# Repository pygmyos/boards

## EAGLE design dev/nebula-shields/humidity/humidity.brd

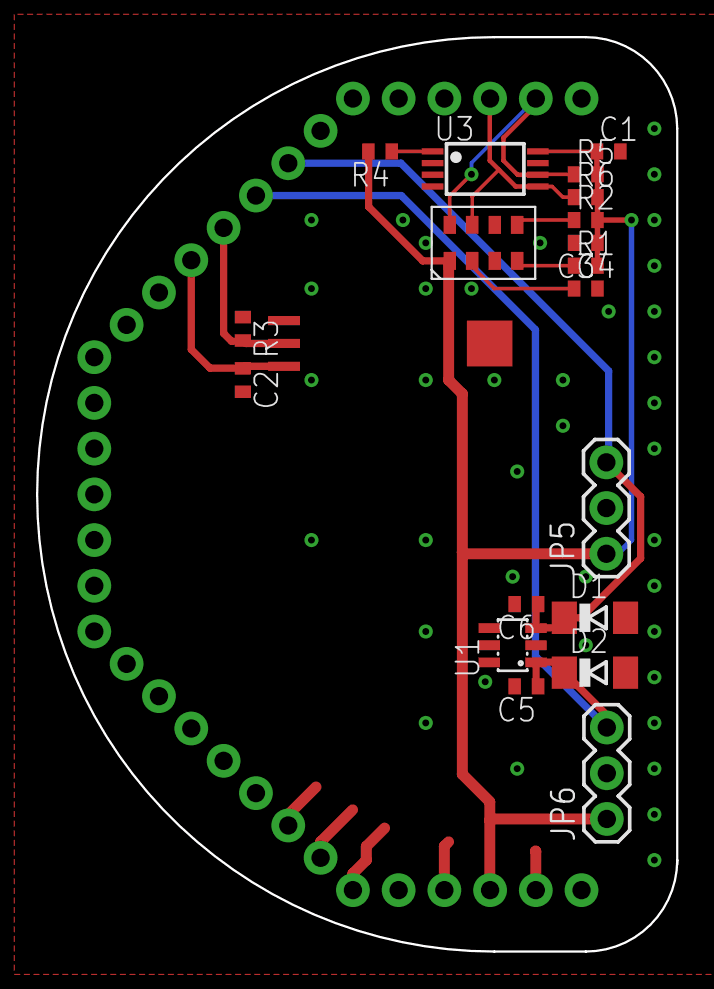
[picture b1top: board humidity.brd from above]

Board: 2 copper layers, 35.6 x 50.8 mm, 24 parts (0 on the bottom side), 12 nets.

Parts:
C1, C2: 0.1uF; C0402
C3, C4: 1uF; C0402
C5, C6: 33pF; C0402
D1, D2: 3.3V; SOD80C
INFO2: Warren D Greenway and Evan Teitelman; %CC-NC-SA
JP5, JP6: JUMPER-3PTH; 1X03
LOGO1: #LOGOA-THICK
NEBULA1: #NEBULAPTH; #NEBULA-PTH@1
NEBULAPART1: #NEBULA-PARTLABELS-BOTTOM; #NEBULA-LABELS-BOTT
R1, R2, R4: 47K; R0402
R3: 15K; R0402
R5, R6: 10K; R0402
U1: ESDAXXSC6; SOT23-6L
U2: HIH-5030
U3: EEPROM-ATMEL-AT24HC02B; TSSOP8
U4: PRESSURE-FREESCALE-MPL115A1; LGA8

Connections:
3.3V: C1.1, C3.1, JP5.1, JP6.1, NEBULA1.3.3V, R1.2, R2.2, R4.2, R5.2, R6.2, U3.8, U4.P1
GND: C1.2, C2.2, C3.2, C4.2, C5.2, C6.2, D1.A, D2.A, JP5.2, JP6.2, NEBULA1.GND1, NEBULA1.GND2, NEBULA1.GND3, NEBULA1.GND4, NEBULA1.GND5, R3.1, U1.2, U1.5, U2.P$2, U3.2, U3.3, U3.4, U3.7, U4.P3
unnamed: R4.1, U3.1
unnamed: C4.1, U4.P2
PWR: C2.1, NEBULA1.A3, U2.P$4
RST: R2.1, U4.P5
SCL: NEBULA1.COM1_TX, R5.1, U3.6, U4.P8
SDA: NEBULA1.COM1_RX, R6.1, U3.5, U4.P7
SENSOR: NEBULA1.A2, R3.2, U2.P$3
SHDN: R1.1, U4.P4
VOLT1: C6.1, D1.C, JP5.3, NEBULA1.A0, U1.3
VOLT2: C5.1, D2.C, JP6.3, NEBULA1.A1, U1.1

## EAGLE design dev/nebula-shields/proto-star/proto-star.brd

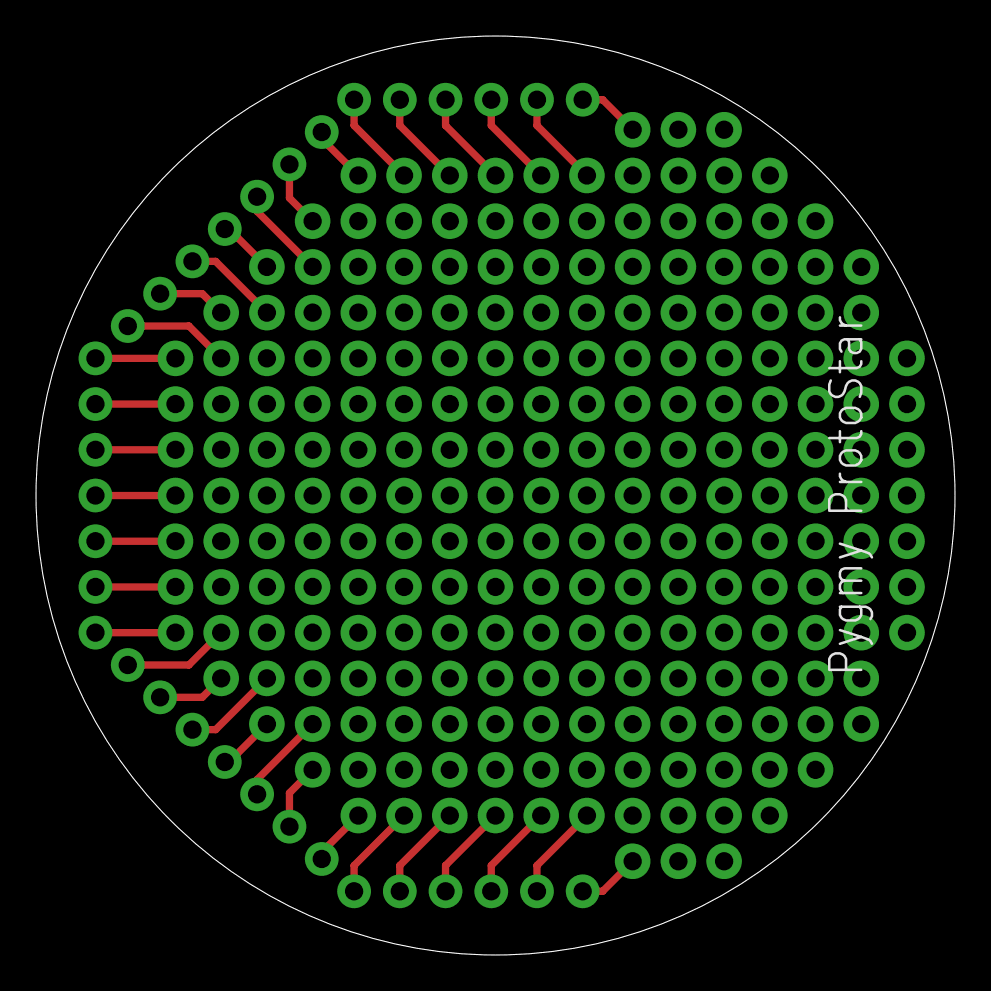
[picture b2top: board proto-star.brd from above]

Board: 2 copper layers, 51.1 x 51.1 mm, 35 parts (0 on the bottom side), 33 nets.

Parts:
FP1: #NEBULAPTH; #NEBULA-PTH
INFO2: Evan Teitelman and Warren D Greenway; %CC-NC-SA
TP1, TP2, TP3, TP4, TP5, TP6, TP7, TP8, TP9, TP10, TP11, TP12, TP13, TP14, TP15, TP16, TP17, TP35, TP36, TP37, TP38, TP39, TP40, TP41, TP42, TP43, TP44, TP45, TP46, TP47, TP48, TP49, TP50: NEBULA-TP

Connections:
unnamed: FP1.MCO, TP1.P$1
unnamed: FP1.COM1_TX, TP2.P$1
unnamed: FP1.COM1_RX, TP3.P$1
unnamed: FP1.T0, TP4.P$1
unnamed: FP1.T1, TP5.P$1
unnamed: FP1.T2, TP6.P$1
unnamed: FP1.T3, TP7.P$1
unnamed: FP1.A0, TP8.P$1
unnamed: FP1.A1, TP9.P$1
unnamed: FP1.A2, TP10.P$1
unnamed: FP1.A3, TP11.P$1
unnamed: FP1.D3, TP12.P$1
unnamed: FP1.D2, TP13.P$1
unnamed: FP1.D1, TP14.P$1
unnamed: FP1.D0, TP15.P$1
unnamed: FP1.A4, TP16.P$1
unnamed: FP1.A5, TP17.P$1
unnamed: FP1.COM2_TX, TP35.P$1
unnamed: FP1.COM2_RX, TP36.P$1
unnamed: FP1.DAC1, TP37.P$1
unnamed: FP1.DAC2, TP38.P$1
unnamed: FP1.TA0, TP39.P$1
unnamed: FP1.TA1, TP40.P$1
unnamed: FP1.A6, TP41.P$1
unnamed: FP1.A7, TP42.P$1
unnamed: FP1.GND5, TP43.P$1
unnamed: FP1.GND4, TP44.P$1
unnamed: FP1.GND3, TP45.P$1
unnamed: FP1.5V, TP46.P$1
unnamed: FP1.GND2, TP47.P$1
unnamed: FP1.3.3V, TP48.P$1
unnamed: FP1.GND1, TP49.P$1
unnamed: FP1.BAT, TP50.P$1

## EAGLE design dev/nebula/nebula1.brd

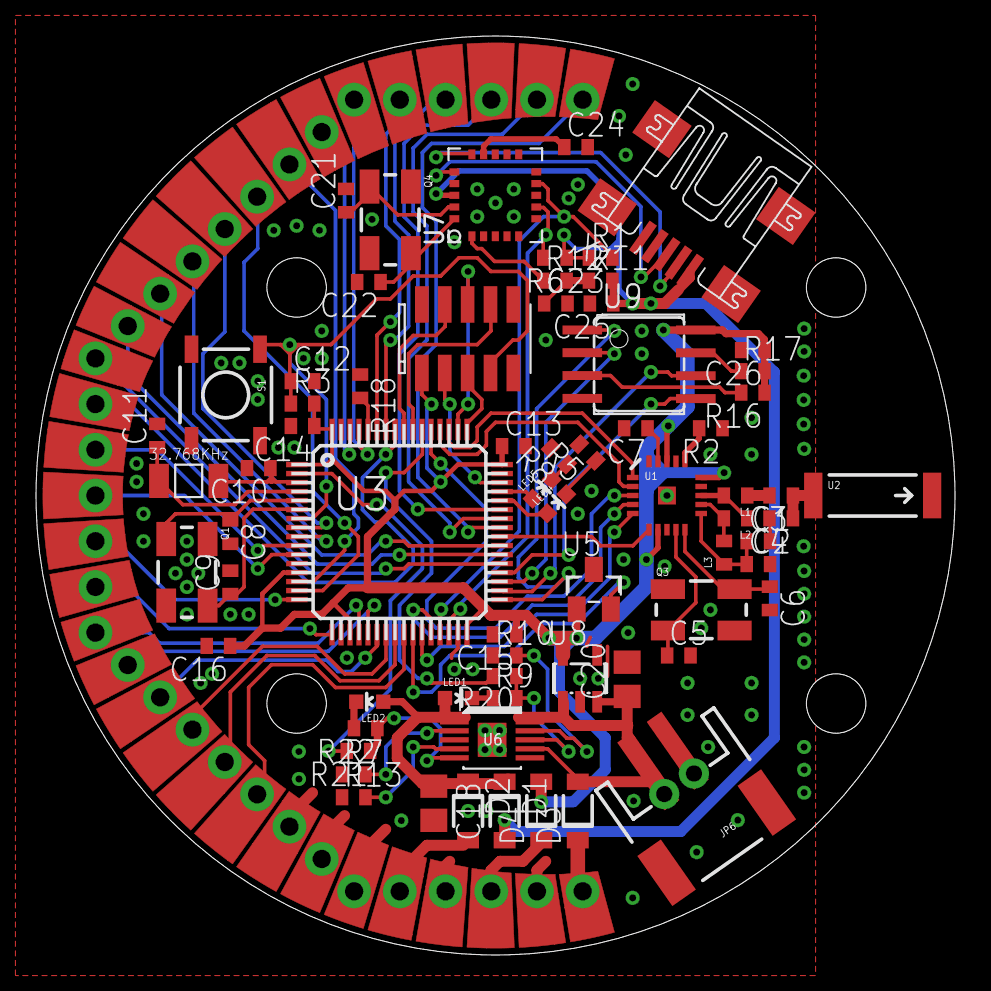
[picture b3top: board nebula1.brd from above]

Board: 2 copper layers, 51.1 x 51.1 mm, 80 parts (1 on the bottom side), 88 nets.

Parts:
C1: 1.5pF; C0402
C2: 1.0pF; C0402
C3: 0.0022uF; C0402
C4: 4.7pF; C0402
C5, C6, C8, C9, C21, C22: 18pF; C0402
C7: 0.033uF; C0402
C10, C11: 9pF; C0402
C12: 220pF; C0402
C13, C14, C15, C16, C23, C25, C26: 0.1uF; C0402
C18, C20: 10uF; C0805
C24: 0.47uF; C0402
D1, D2, D3, D4: SMF5.0AT1; SOD123FL
INFO3: Warren D Greenway and Evan Teitelman; %CC-NC-SA
JP6: JST-2-SMD
L1: 3.9nH; C0402
L2: 8.2nH; C0402
L3: 2.7nH; C0402
LED1: ORANGE; LED-0603
LED2: YELLOW; LED-0603
LED4: BLUE; LED-0603
LED5: GREEN; LED-0603
LOGO1: #LOGOA-THICK
NEBULA1: #NEBULAPTH; #NEBULA-PTH@1
NEBULAPART1: #NEBULA-PARTCOPPER; #NEBULA-COPPER
NEBULAPART2: #NEBULA-PARTRESTRICT; #NEBULA-RESTRICT
NEBULAPART3: #NEBULA-PARTSTOP; #NEBULA-STOP
NEBULAPART4: #NEBULA-PARTLABELS-BOTTOM; #NEBULA-LABELS-BOTT
Q1, Q4: 12MHz; CRYSTAL-SMD-5X3
Q2: CM415
Q3: 16MHz; CRYSTAL-SMD-5X3
R1, R6, R17, R18: 47K; R0402
R2: 22K; R0402
R3, R16: 100K; R0402
R5, R8, R9, R12, R22: 470; R0402
R7, R13: 1K; R0402
R10, R11, R20, R21: 10K; R0402
S1: TACTILE_SWITCH_SMD
U1: NRF24L01SMD; QFN20
U2: ANTENNA2SMD5; ANTENNA-CHIP5
U3: STM32F100R4T6B; S-PQFP64-G64
U4: STM32-JTAG-10P
U5: MICROCHIP-TEMP-TC1047; SOT23
U6: BQ24090; R-PDSO-G10
U7: MICROCHIP-USB-MCP2200; QFN-20-5X5
U8: NCP500; SOT23-5L
U9: SST25VF080B; SOIC8@1
U$1, U$2, U$3, U$4: STAND-OFF
X1: MINI-USB-UX60A-MB-5ST; UX60A-MB-5ST

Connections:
3.3V: C13.1, C14.1, C15.1, C16.1, C26.1, D4.A, R3.2, R16.1, R17.2, U1.7, U1.15, U1.18, U3.1, U3.13, U3.19, U3.32, U3.48, U3.64, U4.1, U5.1, U8.5, U9.8
5V: C18.1, D1.C, D2.C, LED1.A, LED2.A, U6.P$1
A0: NEBULA1.A0, U3.14
A1: NEBULA1.A1, U3.15
A2: NEBULA1.A2, U3.8
A3: NEBULA1.A3, U3.9
A4: NEBULA1.A4, U3.10
A5: NEBULA1.A5, U3.11
A6: NEBULA1.A6, U3.24
A7: NEBULA1.A7, U3.25
BAT: C20.1, D3.A, JP6.2, U6.P$7, U6.P$10, U8.1, U8.3
BAT1: R20.2, U3.54
BAT2: R21.2, U3.2
BOOT0: R18.2, U3.60
COM3_RX: R6.2, U3.30, U7.P7
COM3_TX: R1.2, U3.29, U7.P9
D0: NEBULA1.D0, U3.57
D1: NEBULA1.D1, U3.37
D2: NEBULA1.D2, U3.38
D3: NEBULA1.D3, U3.39
DAC1: NEBULA1.DAC1, U3.20
DAC2: NEBULA1.DAC2, U3.21
FLASH_CS: U3.33, U9.1
FLASH_MISO: U3.35, U9.2
FLASH_MOSI: U3.36, U9.5
FLASH_SCK: U3.34, U9.6
JTCK: U3.49, U4.5
JTDI: U3.50, U4.6
JTDO: U3.55, U4.8
JTMS: U3.46, U4.3
JTRST: U3.56, U4.4
LED0: LED4.A, U3.44
LED1: LED5.A, U3.45
MCO: NEBULA1.MCO, U3.41
unnamed: C1.1, C2.1, U2.FEED
unnamed: C1.2, L1.1
unnamed: L1.2, L2.1, U1.13
unnamed: L2.2, L3.2, U1.12
unnamed: C3.1, C4.1, L3.1, U1.11
unnamed: R17.1, U9.7
unnamed: C6.1, Q3.3, U1.10
unnamed: C5.1, Q3.1, U1.9
unnamed: C2.2, C3.2, C4.2, C5.2, C6.2, C7.2, C8.2, C9.2, C10.2, C11.2, C12.2, C13.2, C14.2, C15.2, C16.2, C18.2, C20.2, C21.2, C22.2, C23.2, C24.2, C25.2, C26.2, JP6.1, NEBULA1.GND1, NEBULA1.GND2, NEBULA1.GND3, NEBULA1.GND4, NEBULA1.GND5, R2.1, R5.2, R7.1, R8.2, R10.1, R13.1, R18.1, S1.3, S1.4, U1.0, U1.8, U1.14, U1.17, U1.20, U3.12, U3.18, U3.31, U3.47, U3.63, U4.2, U4.9, U5.3, U6.P$3, U6.P$11, U7.P17, U8.2, U9.4, X1.5, X1.M1, X1.M2, X1.M3, X1.M4
unnamed: R2.2, U1.16
unnamed: C7.1, U1.19
unnamed: R10.2, U6.P$9
unnamed: D3.C, NEBULA1.BAT
unnamed: R7.2, U6.P$2
unnamed: R13.2, U6.P$4
unnamed: C23.1, R11.1, R12.2
unnamed: C22.1, Q4.3, U7.P20
unnamed: C21.1, Q4.1, U7.P19
unnamed: R12.1, U7.P1
unnamed: U7.P15, X1.2
unnamed: R21.1, R22.1, U6.P$5
unnamed: C24.1, U7.P14
unnamed: D4.C, NEBULA1.3.3V
unnamed: R16.2, U9.3
unnamed: R9.2, R20.1, U6.P$8
unnamed: LED1.C, R9.1
unnamed: LED2.C, R22.2
unnamed: C25.1, D1.A, R1.1, R6.1, R11.2, U7.P18, X1.1
unnamed: LED5.C, R8.1
unnamed: U7.P16, X1.3
unnamed: LED4.C, R5.1
unnamed: D2.A, NEBULA1.5V
OSC32_IN: C10.1, Q2.P$2, U3.3
OSC32_OUT: C11.1, Q2.P$1, U3.4
OSC_IN: C8.1, Q1.1, U3.5
OSC_OUT: C9.1, Q1.3, U3.6
RF24_CS: U1.2, U3.52
RF24_EN: U1.1, U3.51
RF24_IRQ: U1.6, U3.40
RF24_MISO: U1.5, U3.27
RF24_MOSI: U1.4, U3.28
RF24_SCK: U1.3, U3.53
RST: C12.1, R3.1, S1.1, U3.7, U4.7
RX1: NEBULA1.COM1_RX, U3.43
RX2: NEBULA1.COM2_RX, U3.17
T0: NEBULA1.T0, U3.58
T1: NEBULA1.T1, U3.59
T2: NEBULA1.T2, U3.61
T3: NEBULA1.T3, U3.62
TA0: NEBULA1.TA0, U3.22
TA1: NEBULA1.TA1, U3.23
TEMP: U3.26, U5.2
TX1: NEBULA1.COM1_TX, U3.42
TX2: NEBULA1.COM2_TX, U3.16

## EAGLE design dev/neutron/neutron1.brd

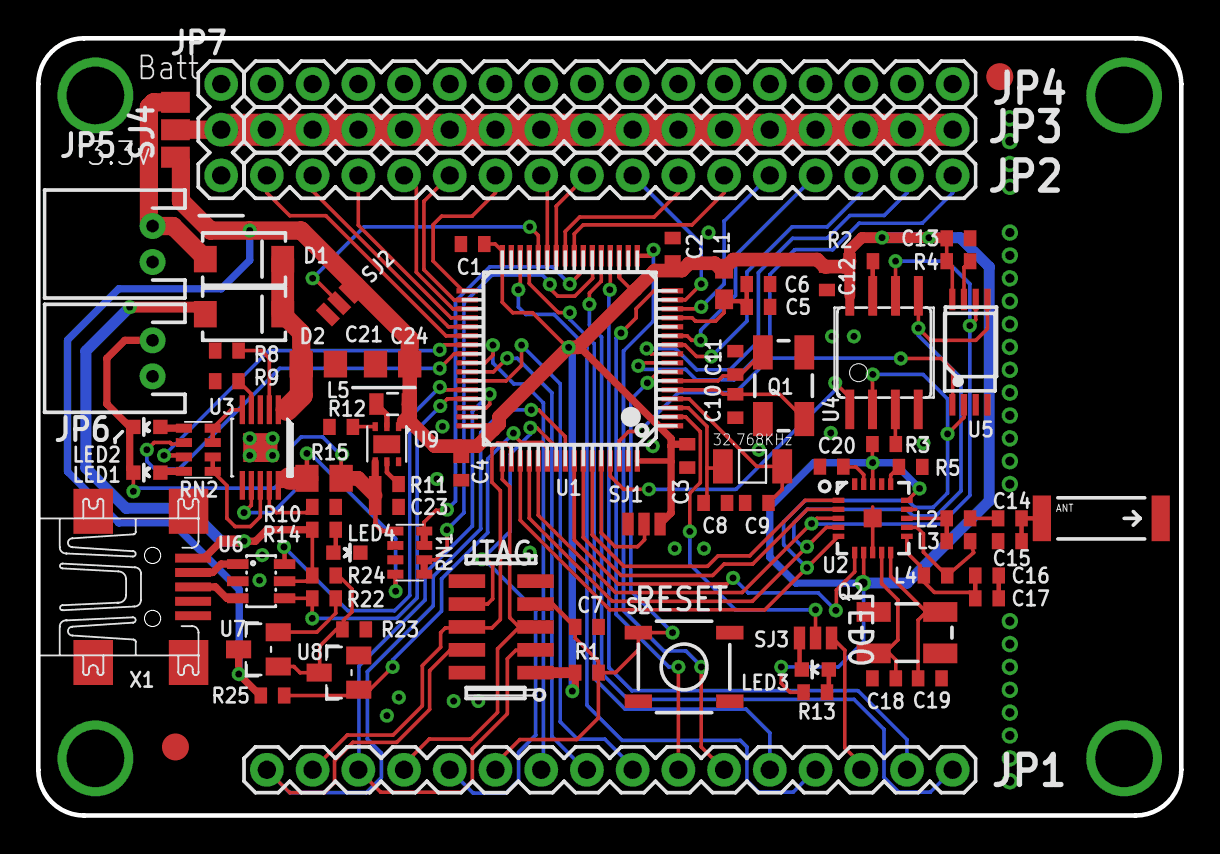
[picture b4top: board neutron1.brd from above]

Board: 2 copper layers, 63.5 x 43.2 mm, 83 parts (0 on the bottom side), 92 nets.

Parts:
ANT: ANTENNA2SMD5; ANTENNA-CHIP5
C1, C2, C3, C4, C5, C12, C13: 0.1uF; C0402
C6, C23: 2.2uF; C0402
C7: 220pF; C0402
C8, C9: 18pF; C0402
C10, C11, C18, C19: 12.5pF; C0402
C14: 1.5pF; C0402
C15: 1.0pF; C0402
C16: 4.7pF; C0402
C17: 0.0022uF; C0402
C20: 0.033uF; C0402
C21, C24: 10uF; C0805
D1, D2: DIODE-SCHOTTKY_; SMA-DIODE
INFO4: Warren D Greenway and Evan Teitelman; %CC-NC-SA
JP1, JP2, JP3, JP4: M16ALTSILKLAYER; 1X16SS
JP5, JP6: JST-2-PTH
JP7: 1X03SS
JP8, JP9: FIDUCIAL1.5X3; FIDUCIAL-1.5X3
L1: 10uH; 0603
L2: 3.9nH; C0402
L3: 8.2nH; C0402
L4: 2.7nH; C0402
L5: 1uH; 0805
LED1, LED2, LED3, LED4: LED-0603
Q1: 8MHz; CRYSTAL-SMD-5X3
Q2: 16MHz; CRYSTAL-SMD-5X3
R1, R2, R3, R4: 100K; R0402
R5: 22K; R0402
R8, R9: 1K; R0402
R10, R24: 10K; R0402
R11, R12, R25: 47K; R0402
R13: 330; R0402
R14: 470; R0402
R15: 0.1; R0805
R22: 1.5K; R0402
R23: 36K; R0402
RN1, RN2: CTS742C083
S2: SWITCH-MOMENTARY-2SMD; SPARKFUN_TACTILE_SWITCH_SMD
SJ1, SJ2, SJ3: SJ_3
SJ4: SJ_2
U1: STM32L152; S-PQFP64-G64
U2: NRF24L01SMD; QFN20
U3: BQ24090; R-PDSO-G10
U4: SST25VF080B; DUBLIB_SOIC8
U5: N25S0830HA; TSSOP8
U6: USBLC6-2; SOT23-6L
U7, U8: BIPOLAR-PMBT6428; DUBLIB_SOT23
U9: FAIRCHILD-REG-FAN5362; MO229
U10: CM415
U$2: STM32-JTAG-10P
X1: MINI-USBUX60-MB-5ST; DUBLIB_UX60-MB-5ST

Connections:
+3V3: C1.1, C2.1, C3.1, C4.1, C12.1, C13.1, C24.1, L1.2, L5.1, R1.2, R2.2, R3.2, R4.2, R13.2, R25.1, SJ1.3, SJ2.3, SJ4.1, U1.1, U1.19, U1.32, U1.48, U1.64, U2.7, U2.15, U2.18, U4.8, U5.8, U7.3, U9.P1, U$2.1
+5V: D2.A, R14.2, R24.1, U6.5, X1.1
A0: JP2.10, U1.25
A1: JP2.11, U1.24
A2: JP2.12, U1.14
A3: JP2.13, U1.11
A4: JP2.14, U1.10
A5: JP2.15, U1.9
A6: JP2.16, U1.8
BAT_CHG: RN2.7, U1.39
BAT_LVL1: RN1.1, RN1.2, U1.22
BAT_LVL2: RN1.3, RN1.4, U1.23
BAT_PG: RN2.6, U1.40
BOOT0: SJ1.2, U1.60
BOOT1: SJ2.2, U1.28
COM1_RX: JP1.9, U1.43
COM1_TX: JP1.8, U1.42
COM2_RX: JP1.11, U1.17
COM2_TX: JP1.10, U1.16
COM3_RX: JP1.13, U1.30
COM3_TX: JP1.12, U1.29
DAC1: JP1.15, U1.20
DAC2: JP1.16, U1.21
FLASH_CS: U1.61, U4.1
FLASH_HOLD: R2.1, U4.7
FLASH_WP: R3.1, U4.3
GND: C1.2, C2.2, C3.2, C4.2, C5.2, C6.2, C7.2, C8.2, C9.2, C10.2, C11.2, C12.2, C13.2, C15.2, C16.2, C17.2, C18.2, C19.2, C20.2, C21.2, C23.2, C24.2, JP4.1, JP4.2, JP4.3, JP4.4, JP4.5, JP4.6, JP4.7, JP4.8, JP4.9, JP4.10, JP4.11, JP4.12, JP4.13, JP4.14, JP4.15, JP4.16, JP5.1, JP6.1, JP7.1, LED4.C, R5.1, R8.1, R9.1, R10.2, R12.1, R23.2, RN1.6, RN1.7, S2.3, SJ1.1, SJ2.1, U1.12, U1.18, U1.31, U1.47, U1.63, U2.0, U2.8, U2.14, U2.17, U2.20, U3.P$3, U3.P$11, U4.4, U5.4, U6.2, U8.2, U9.P6, U9.PAD, U$2.2, U$2.9, X1.4, X1.5, X1.M1, X1.M2, X1.M3, X1.M4
JTCK: JP1.4, U1.49, U$2.5
JTDI: JP1.2, U1.50, U$2.6
JTDO: JP1.5, U1.55, U$2.8
JTMS: JP1.3, U1.46, U$2.3
JTRST: JP1.1, U1.56, U$2.4
LED0: JP1.14, SJ3.1
MCO: JP1.7, U1.41
unnamed: C5.1, C6.1, L1.1, U1.13
unnamed: C8.1, U1.3, U10.P$1
unnamed: C9.1, U1.4, U10.P$2
unnamed: C10.1, Q1.1, U1.5
unnamed: C11.1, Q1.3, U1.6
unnamed: L3.2, L4.2, U2.12
unnamed: ANT.FEED, C14.1, C15.1
unnamed: C14.2, L2.1
unnamed: L2.2, L3.1, U2.13
unnamed: C16.1, C17.1, L4.1, U2.11
unnamed: C20.1, U2.19
unnamed: R5.2, U2.16
unnamed: C18.1, Q2.1, U2.9
unnamed: C19.1, Q2.3, U2.10
unnamed: R10.1, U3.P$9
unnamed: RN2.3, RN2.4, U3.P$5
unnamed: R9.2, U3.P$4
unnamed: R8.2, U3.P$2
unnamed: LED1.A, RN2.8
unnamed: LED2.A, RN2.5
unnamed: RN2.1, RN2.2, U3.P$8
unnamed: JP3.1, JP3.2, JP3.3, JP3.4, JP3.5, JP3.6, JP3.7, JP3.8, JP3.9, JP3.10, JP3.11, JP3.12, JP3.13, JP3.14, JP3.15, JP3.16, JP7.2, SJ4.2
unnamed: U6.3, X1.3
unnamed: U6.1, X1.2
unnamed: L5.2, U9.P2
unnamed: LED4.A, R14.1
unnamed: R11.1, U9.P5
unnamed: R12.2, U9.P3
unnamed: C21.1, D1.C, D2.C, U3.P$1
unnamed: LED3.C, SJ3.3
unnamed: LED3.A, R13.1
unnamed: R15.1, RN1.8, U3.P$7, U3.P$10
unnamed: R23.1, R24.2, U7.1, U8.3
unnamed: R22.1, U7.2
PC13: SJ3.2, U1.2
RF24_CE: U1.59, U2.1
RF24_CS: U1.58, U2.2
RF24_IRQ: U1.57, U2.6
RST: C7.1, JP1.6, R1.1, S2.1, U1.7, U$2.7
SPI_MISO: U1.51, U2.5, U4.2, U5.2
SPI_MOSI: U1.52, U2.4, U4.5, U5.5
SPI_SCK: U1.53, U2.3, U4.6, U5.6
SRAM_CS: U1.62, U5.1
SRAM_HOLD: R4.1, U5.7
T0: JP2.1, U1.38
T1: JP2.2, U1.37
TA0: JP2.3, U1.36
TA1: JP2.4, U1.35
TA2: JP2.5, U1.34
TA3: JP2.6, U1.33
TA4: JP2.7, U1.27
TA5: JP2.8, U1.26
TA6: JP2.9, U1.15
USB_DISC: R25.2, U1.54, U8.1
USB_DM: U1.44, U6.6
USB_DP: R22.2, U1.45, U6.4
V+: D1.A, JP5.2, SJ4.3
VCC: C23.1, JP6.2, LED1.C, LED2.C, R11.2, R15.2, RN1.5, U9.P4

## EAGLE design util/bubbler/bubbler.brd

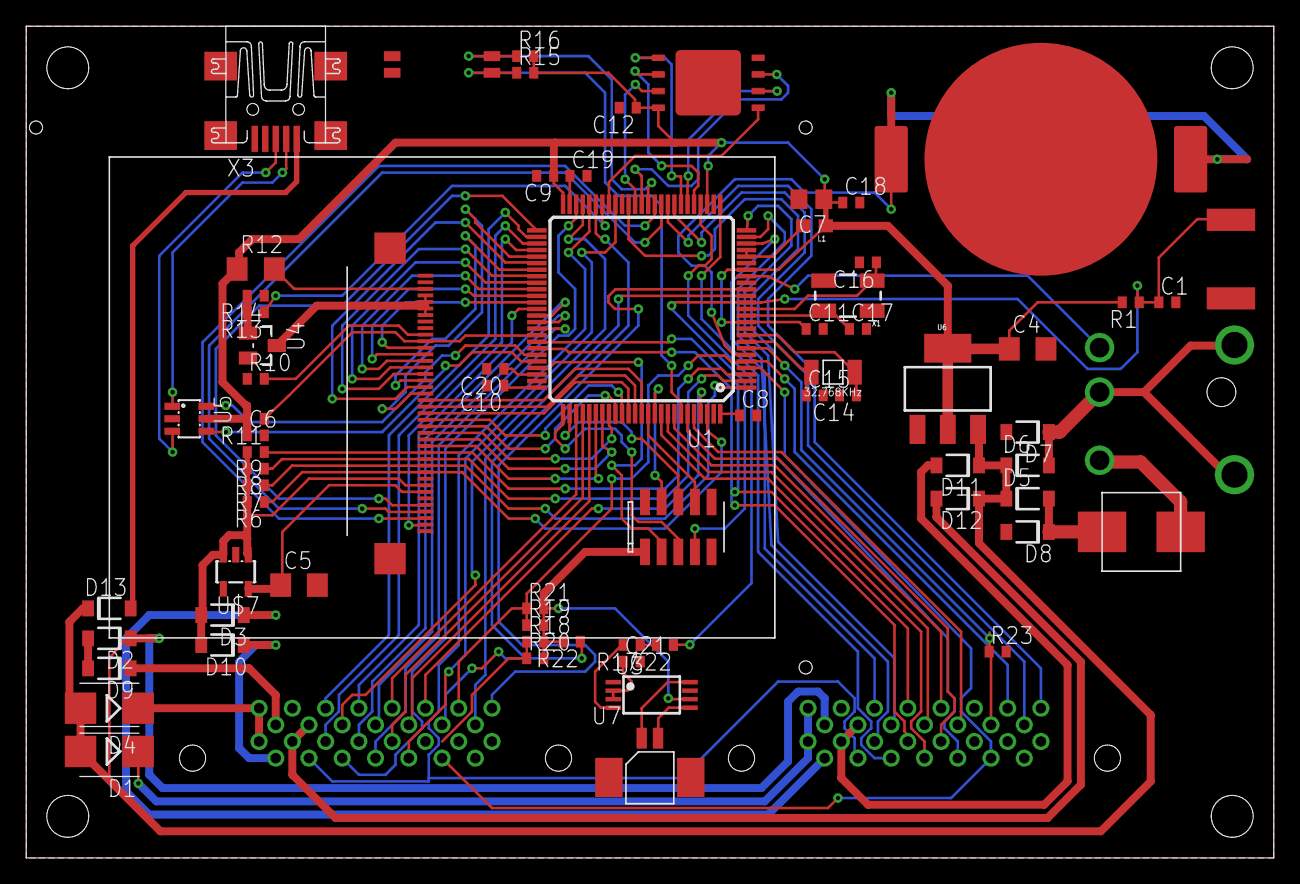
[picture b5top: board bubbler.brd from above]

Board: 2 copper layers, 95.2 x 63.5 mm, 73 parts (0 on the bottom side), 114 nets.

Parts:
B1: BATTERY-LINX-HLD-001
C1: 220pF; C0402
C4, C5: 10uF; C1206
C6, C8, C9, C10, C11, C12, C18, C19, C20: 0.1uF; C0402
C7: 10uF; C0805
C14, C15, C16: 18pF; C0402
C17: 18pf; C0402
C21: 1uF; C0402
C22: 0.39uF; C0402
CARD0, CARD1: CONNECTOR-JAE-TX24-30F; CONNECTOR-JAE-TX24-30
D1, D4: SMB
D2, D3, D5, D6, D7, D8, D9, D10, D11, D12, D13: SMF5.0AT1; SOD123FL
F1: BOURNES-PTC-MF-SMXXXMF-SM030; MF-SM030
L1: 0603
R1, R10, R11, R14, R15, R16, R22, R23: 47K; R0402
R6, R7, R8, R9, R18, R19, R20, R21: 10K; R0402
R12: 330; R1206
R13: 1K; R0402
R17: 20K; R0402
SW1: SWITCH-DIP-GDH-02
SW2: ITT-SWITCH-KSS-G; ITT-KSS-G
U1: STM32F41X-100P; TQFP100
U2: SPANSION-S25FL256; SPANSION-WSON-8
U3: LM4890; TSSOP8
U4: BIPOLAR-PMBT6428; DUBLIB_SOT23
U5: USBLC6-2; SOT23-6L
U6: TLV1117; SOT223
U7: MOLEX-1.25-WTB-RA-CONN-2POS; MOLEX-1.25WTB-RA-CONN
U$1: STM32-JTAG-10P
U$2: DCJACK-CUI-PJ051AH; DCJACK_CUI_PJ012B
U$3: NHD-2.4-240320SF-OUTLINE
U$7: NCP500; SOT23-5L
U$10: NHD-2.4-240320SF; MOLEX-534132-060
X1: CRYSTAL-SMD-5X3
X2: CM415
X3: MINI-USBUX60-MB-5ST; DUBLIB_UX60-MB-5ST

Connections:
2.8V: C5.1, U$7.5, U$10.P34
3.3V: C4.1, C6.1, C7.1, C8.1, C9.1, C10.1, C11.1, C12.1, C18.1, D3.A, D10.A, L1.1, R1.2, R6.2, R7.2, R8.2, R9.2, R11.2, R12.1, R15.2, R16.2, R18.2, R19.2, R20.2, R21.2, R22.2, U1.11, U1.19, U1.28, U1.50, U1.75, U1.100, U2.P8, U3.6, U5.5, U6.2, U6.4, U$1.1, U$7.1, U$7.3, U$10.P33
+5V: D2.A, D9.A
AUDIO_OUT: C22.1, U1.29
BAT: B1.P1, B1.P2, U1.6
BOOT0: R15.1, SW1.P1, U1.94
BOOT1: R16.1, SW1.P2, U1.37
CARD0_INSERT: CARD0.P23, R23.1, U1.7
CARD1_INSERT: CARD1.P23, R22.1, U1.45
CARD_SCL: CARD0.P24, CARD1.P24, R18.1, R20.1, U1.4
CARD_SDA: CARD0.P25, CARD1.P25, R19.1, R21.1, U1.5
EXT0_0: CARD0.P9, U1.23
EXT0_1: CARD0.P10, U1.24
EXT0_2: CARD0.P11, U1.25
EXT0_3: CARD0.P12, U1.26
EXT0_4: CARD0.P13, U1.68
EXT0_5: CARD0.P14, U1.69
EXT0_6: CARD0.P15, U1.92
EXT0_7: CARD0.P16, U1.91
EXT0_8: CARD0.P17, U1.93
EXT0_9: CARD0.P18, U1.95
EXT0_10: CARD0.P19, U1.96
EXT0_11: CARD0.P20, U1.40
EXT0_ADC0: CARD0.P27, U1.33
EXT0_ADC1: CARD0.P29, U1.34
EXT1_0: CARD1.P9, U1.52
EXT1_1: CARD1.P10, U1.53
EXT1_2: CARD1.P11, U1.47
EXT1_3: CARD1.P12, U1.48
EXT1_4: CARD1.P13, U1.63
EXT1_5: CARD1.P14, U1.64
EXT1_6: CARD1.P15, U1.65
EXT1_7: CARD1.P16, U1.66
EXT1_8: CARD1.P17, U1.78
EXT1_9: CARD1.P18, U1.79
EXT1_10: CARD1.P19, U1.80
EXT1_11: CARD1.P20, U1.42
EXT1_12: CARD1.P21, U1.41, U1.97
EXT1_ADC0: CARD1.P27, U1.15
EXT1_ADC1: CARD1.P29, U1.16
FLASH_CS: U1.43, U2.P1
FLASH_IO0: U1.32, U2.P5
FLASH_IO1: U1.31, U2.P2
FLASH_IO2: U1.38, U2.P3
FLASH_IO3: U1.39, U2.P7
FLASH_SCK: U1.30, U2.P6
GND: B1.PAD, C1.2, C4.2, C5.2, C6.2, C7.2, C8.2, C9.2, C10.2, C11.2, C12.2, C14.2, C15.2, C16.2, C17.2, C18.2, C19.2, C20.2, C21.2, CARD0.P5, CARD0.P22, CARD0.P26, CARD0.P28, CARD0.P30, CARD1.P5, CARD1.P22, CARD1.P26, CARD1.P28, CARD1.P30, D7.A, D8.A, R10.1, R14.1, R23.2, SW1.P3, SW1.P4, SW2.P$1, U1.10, U1.20, U1.27, U1.74, U1.99, U2.P4, U3.7, U4.2, U5.2, U6.1, U7.P$3, U7.P$4, U$1.9, U$7.2, U$10.P2, U$10.P8, U$10.P40, X3.4, X3.5, X3.M1, X3.M2, X3.M3, X3.M4
JTCK: U1.76, U$1.5
JTDI: U1.77, U$1.6
JTDO: U1.89, U$1.8
JTMS: U1.72, U$1.3
LCD_BL: R13.1, U1.44
LCD_CS: R6.1, U1.98, U$10.P31
LCD_DB0: U1.81, U$10.P27
LCD_DB1: U1.82, U$10.P26
LCD_DB2: U1.83, U$10.P25
LCD_DB3: U1.84, U$10.P24
LCD_DB4: U1.85, U$10.P23
LCD_DB5: U1.86, U$10.P22
LCD_DB6: U1.87, U$10.P21
LCD_DB7: U1.88, U$10.P20
LCD_DB8: U1.55, U$10.P19
LCD_DB9: U1.56, U$10.P18
LCD_DB10: U1.57, U$10.P17
LCD_DB11: U1.58, U$10.P16
LCD_DB12: U1.59, U$10.P15
LCD_DB13: U1.60, U$10.P14
LCD_DB14: U1.61, U$10.P13
LCD_DB15: U1.62, U$10.P12
LCD_RD: R9.1, U1.3, U$10.P28
LCD_RESET: R11.1, U1.67, U$10.P11
LCD_RS: R7.1, U1.1, U$10.P30
LCD_WR: R8.1, U1.2, U$10.P29
LCD_X+: U1.36, U$10.P38
LCD_X-: U1.51, U$10.P36
LCD_Y+: U1.35, U$10.P37
LCD_Y-: U1.54, U$10.P39
unnamed: CARD1.P4, D10.C
unnamed: D6.A, D7.C, U$2.GND1, U$2.GND2, U$2.P2
unnamed: F1.P$1, U$2.P1
unnamed: R10.2, U$10.P10
unnamed: U5.1, X3.2
unnamed: U5.3, X3.3
unnamed: D5.A, D8.C, F1.P$2
unnamed: R12.2, U$10.P3
unnamed: CARD0.P4, D3.C
unnamed: U4.3, U$10.P4, U$10.P5, U$10.P6, U$10.P7
unnamed: L1.2, U1.21, U1.22
unnamed: C19.1, U1.49
unnamed: R13.2, R14.2, U4.1
unnamed: C20.1, U1.73
unnamed: CARD0.P1, CARD0.P2, D1.C
unnamed: U3.5, U7.P$2
unnamed: U3.8, U7.P$1
unnamed: C21.1, U3.2, U3.3
unnamed: R17.2, U3.4
unnamed: C22.2, R17.1
unnamed: CARD1.P1, CARD1.P2, D4.C
unnamed: CARD0.P3, D2.C
unnamed: CARD0.P6, CARD0.P7, D11.A
unnamed: CARD1.P3, D9.C
unnamed: D13.A, X3.1
unnamed: CARD1.P6, CARD1.P7, D12.A
NJTRST: U1.90, U$1.4
NRST: C1.1, R1.1, SW2.P$2, U1.14, U$1.7
OSC32_IN: C15.1, U1.8, X2.P$2
OSC32_OUT: C14.1, U1.9, X2.P$1
OSC_IN: C17.1, U1.12, X1.3
OSC_OUT: C16.1, U1.13, X1.1
PWR_BAT: CARD0.P8, CARD1.P8, U1.46
PWR_CHG: U1.18, U$2.P3
USB_DM: U1.70, U5.6
USB_DP: U1.71, U5.4
VIN: D1.A, D4.A, D5.C, D6.C, D11.C, D12.C, D13.C, U6.3

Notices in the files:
parts and their libraries:
PygmyBoards: Released under the Creative Commons Attribution-NonCommercial-ShareAlike 3.0 License.
PygmyBoards: http://creativecommons.org/licenses/by-nc-sa/3.0
SparkFun-FreqCtrl: Licensing: CC v3.0 Share-Alike You are welcome to use this library for commercial purposes.
